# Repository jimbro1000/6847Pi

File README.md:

# Motorola 6847P Replacement #

## Background ##

The 6847P is fairly ubiquitous in the history of 70s/80s home computers and while it provides a simple solution to
video signal generation although with fairly basic capabilities in comparison with the custom video solutions
of other 80s home computers.

In terms of availability, the chip is easily obtained and due to reliability, rarely needs replacing. Compared
with the Sinclair ULA or Commodore VIC chips this is a bulletproof system *but* reliability does not equate to
desirability.

The PAL version of the output generated has a very limited palette when in higher resolution modes, the NTSC
version of the output utilises video artifacts to provide a wider capability but is still well behind its
competitors.

## Building a better 6847 ##

There are a number of things that can be done to improve on the design and the availability of high performance,
cheap microcontrollers means it is fairly simple to build a custom VDG that exhibits the same external behaviour
while operating in a completely custom manner internally.

Custom fonts are a basic starting point, custom palettes are equally simple but there is scope in the system to
incorporate custom modes of operation provided the same addressing and timing is retained.

The essential requirement is to replace the 6847P in the Dragon range of home computers - this significantly
narrows the functional requirements of the substitute. In this scenario all addressing is performed by the
accompanying SAM (MC6883) address multiplexing chip. The system also binds pins to further simplify
implementation - INV and DD6 are combined, as are ~A/S and DD7, and ~INT/EXT with GM0. Without this there are
simply not enough GPIO pins available on the pre-built RP Pico board (as opposed to the RP2040 chip itself).

## Objectives ##

1. MVP is to reproduce the existing 6847 as per the original Motorola datasheet using the RP2040 microcontroller
2. Add custom font definition
3. Modify palette definitions per mode
4. Create custom video modes following original timing
5. Create custom video modes with novel screen construction and timing

## Signal Output ##

The 6847 provides 13 lanes of address bus to reference memory - this maps to the first 8k of the regular 16bit
address space. If used in conjunction with the MC6883 SAM chip only the first bit is used to provided a clock
signal to an internal address counter. This allows the use of paged video memory - all on 512 byte boundaries,
potentially anywhere in the full 64k address space.

In addition, the chip provides a horizontal sync signal (consumed by the SAM)

Fully implemented the data output requires 14 gpio pins. Simplifying the implementation in conjunction with a
SAM reduces the pin count to just 2.

## Signal Input ##

The 6847 requires a clock input (CLK), 8 bits of data bus (DD0-DD7) and 8 bits of mode control:

* ~A/G = Alpha or Graphics
* ~A/S = Alpha or Semigraphics
* ~INT/EXT = Internal or External alphanumerics
* GM0 = Graphic Mode LSB
* GM1 = Graphic Mode Bit 1
* GM2 = Graphic Mode Bit 2 (MSB)
* CSS
* INV = Inverted Alphanumerics

~A/G, ~A/S, CSS and INV can be controlled on a character by character basis.

CSS selects between two possible alphanumeric colours - the effect
will vary depending on the graphic mode selected

| ~A/G | ~A/S | ~INT/EXT | INV | GM2 | GM1 | GM0 | Mode                           | Colours | Page Size |
|:----:|:----:|:--------:|:---:|:---:|:---:|:---:|:-------------------------------|:-------:|:---------:|
|  0   |  0   |    0     |  0  |  X  |  X  |  X  | Internal Alphanumeric          |    2    |    512    |
|  0   |  0   |    0     |  1  |  X  |  X  |  X  | Internal Alphanumeric Inverted |    2    |    512    |
|  0   |  0   |    1     |  0  |  X  |  X  |  X  | External Alphanumeric          |    2    |    512    |
|  0   |  0   |    1     |  1  |  X  |  X  |  X  | External Alphanumeric Inverted |    2    |    512    |
|  0   |  1   |    0     |  X  |  X  |  X  |  X  | Semigraphics 4                 |    8    |   1024    |
|  0   |  1   |    1     |  X  |  X  |  X  |  X  | Semigraphics 6                 |    8    |   2048    |
|  1   |  X   |    X     |  X  |  0  |  0  |  0  | 64x64 Graphics                 |    4    |   1024    |
|  1   |  X   |    X     |  X  |  0  |  0  |  1  | 128x64 Graphics                |    2    |   1024    |
|  1   |  X   |    X     |  X  |  0  |  1  |  0  | 128x64 Graphics                |    4    |   2048    |
|  1   |  X   |    X     |  X  |  0  |  1  |  1  | 128x96 Graphics                |    2    |   1536    |
|  1   |  X   |    X     |  X  |  1  |  0  |  0  | 128x96 Graphics                |    4    |   3072    |
|  1   |  X   |    X     |  X  |  1  |  0  |  1  | 128x192 Graphics               |    2    |   3072    |
|  1   |  X   |    X     |  X  |  1  |  1  |  0  | 128x192 Graphics               |    4    |   6144    |
|  1   |  X   |    X     |  X  |  1  |  1  |  1  | 256x192 Graphics               |    2    |   6144    |

The control input consumes 15 GPIO pins.

## Video Output ##

The 6847 has three output lines - Luminance (Y), ∅ A and ∅ B.

The three signals combine to provide 9 colours - black, green, yellow, blue, red, buff (white), cyan, magenta
and orange.

Y is a 6 level analogue signal, A is a 3 level analogue signal, B is a 4 level analogue signal. Not all signal
combinations are valid for the primary display area. For the main display only 4 levels are needed, the other
two levels are used for signal blanking and sync.

| Colour  | Y |  A  | B |  
|:--------|:-:|:---:|:-:|  
| Black   | 5 | 0/1 | 2 |  
| Green   | 1 |  0  | 0 |  
| Yellow  | 0 |  1  | 0 |  
| Blue    | 2 |  1  | 3 |  
| Red     | 2 |  2  | 2 |  
| Buff    | 0 |  1  | 2 |  
| Cyan    | 1 |  0  | 2 |  
| Magenta | 1 |  2  | 3 |  
| Orange  | 1 |  2  | 0 |  

Using the original datasheet for reference the default output is for NTSC and requires a timing phase
difference between the Y, A and B signals. Y leads the trio, B follows, then A. The Y-B delay is half
the rise/fall time of Y, while the B-A delay is fully the sum of Y-B and the rise/fall time of B.

To achieve an analogue signal output from the microcontroller the signal must be synthesized from a
group of digital GPIO pins.

For the 6 level Y output 3 pins are needed (actually achieves 8 levels). For A and B where 3 or 4 levels are
required then just 2 gpio pins each is needed. This consumes a total of 7 GPIO pins.

## Total GPIO Pin Requirements ##

Data input needs 14 or 2 GPIO pins - for the purposes of the MVP this will use the simple 2 pin
version. Control input requires 15 GPIO pins. Video output requires 7 pins. The grand total of 24 pins.

The initial choice of the RP2040 provides 30 GPIO pins - this is adequate for the simple implementation but is
inadequate for the full pin requirement of 36 pins.

### 6847 to GPIO pin mapping ###

|  6847 pin   |   RP2040 pin    |   RP Pico Pin    |
|:-----------:|:---------------:|:----------------:|
|    VSS 1    |     VSS 57      |      Gnd 38      |
|    DD6 2    |     GPIO6 8     |      GP6 9       |
|    DD0 3    |     GPIO0 2     |      GP0 1       |
|    DD1 4    |     GPIO1 3     |      GP1 2       |
|    DD2 5    |     GPIO2 4     |      GP2 4       |
|    DD3 6    |     GPIO3 5     |      GP3 5       |
|    DD4 7    |     GPIO4 6     |      GP4 6       |
|    DD5 8    |     GPIO5 7     |      GP5 7       |
|    CHB 9    |     GPIO11      |     GP11 15      |
|    B 10     | GPIO18-19 29-30 |  GP18-19 24-25   |
|    A 11     | GPIO20-21 31-32 |  GP20-21 26-27   |
|   ~MS 12    |    GPIO13 16    |     GP13 17      |
|   DA5 13    |        -        |        -         |
|   DA6 14    |        -        |        -         |
|   DA7 15    |        -        |        -         |
|   DA8 16    |        -        |        -         |
|   VCC 17    |        ?        |     Vbus 40      |
|   DA9 18    |        -        |        -         |
|   DA10 19   |        -        |        -         |
|   DA11 20   |        -        |        -         |
|   DA12 21   |        -        |        -         |
|   DA0 22    |    GPIO17 28    |     GP17 22      |
|   DA1 23    |        -        |        -         |
|   DA2 24    |        -        |        -         |
|   DA3 25    |        -        |        -         |
|   DA4 26    |        -        |        -         |
|   GM2 27    |    GPIO10 13    |     GP10 14      |
|    Y 28     | GPIO26-28 38-40 | GP26-28 31,32,34 |
|   GM1 29    |    GPIO9 12     |      GP9 12      |
|   GM0 30    |    GPIO8 11     |      GP8 11      |
| ~INT/EXT 31 |    GPIO8 11     |      GP8 11      |
|   INV 32    |     GPIO6 8     |      GP6 9       |
|   CLK 33    |    GPIO15 18    |     GP15 20      |
|   ~A/S 34   |     GPIO7 9     |      GP7 10      |
|   ~A/G 35   |    GPIO14 17    |     GP14 19      |
|   ~RP 36    |        -        |        -         |
|   ~FS 37    |    GPIO13 16    |     GP13 17      |
|   ~HS 38    |    GPIO16 27    |     GP16 21      |
|   CSS 39    |    GPIO17 28    |     GP17 22      |
|   DD7 40    |     GPIO7 9     |      GP7 10      |

Unused GPIO pins: 12 22 (23 24)

## 6847 video output levels ##

| Color       |  Y    | phi A | phi B |
|:------------|:-----:|:-----:|:-----:|
| Green       | 0.54  | 1.0   | 1.0   |
| Yellow      | 0.42  | 1.0   | 1.5   |
| Blue        | 0.72  | 2.0   | 1.5   |
| Red         | 0.72  | 1.5   | 2.0   |
| Buff        | 0.42  | 1.5   | 1.5   |
| Cyan        | 0.54  | 1.5   | 1.5   |
| Magenta     | 0.54  | 2.0   | 2.0   |
| Orange      | 0.54  | 1.0   | 2.0   |
| Black       | 0.72  | 1.5   | 1.5   |
| Dark Green  | 0.72  | 1.0   | 1.0   |
| Dark Orange | 0.72  | 1.0   | 2.0   |

Values for Y, phi A and phi B are in volts

### Y DAC ###

The 3 GPIO outputs can be converted to an analogue output using a resistor ladder array

GPIO 26 - 2kohm

GPIO 27 - 1kohm

GPIO 28 - 499ohm

Result is 8 levels from 0 to 7 - only the values 0 to 5 are needed. The output at level
5 needs to be peak output, to achieve this some level mapping is needed.

| level | pin 2 | pin 1 | pin 0 | target | output |
|:-----:|:-----:|:-----:|:-----:|:------:|:------:|
| 0     | 0     | 0     | 0     | 0%     | 0%     |
| 1     | 0     | 0     | 1     | 20%    | 14.2%  |
| 2     | 0     | 1     | 1     | 40%    | 42.8%  |
| 3     | 1     | 0     | 0     | 60%    | 57.1%  |
| 4     | 1     | 1     | 0     | 80%    | 85.7%  |
| 5     | 1     | 1     | 1     | 100%   | 100%   |

### A and B DAC ###

The outputs both use the same arrangement with just 2 pins each

GPIO 18, 20 - 1kohm

GPIO 19, 21 - 499ohm

Result on each pair is 4 levels from 0 to 3

The output for B can be direct but A only needs 3 levels which needs
mapping again.

| level | pin 21 | pin 20 | target | output |
|:-----:|:------:|:------:|:------:|:------:|
| 0     | 0      | 0      | 0%     | 0%     |
| 1     | 1      | 0      | 50%    | 66.6%  |
| 2     | 1      | 1      | 100%   | 100%   |

## Phase 2 ##

The next objective of development is to replace the LM889 composite modulator with the more modern AD724JR,
the important detail here is that the AD724JR requires an RGB input instead of the YAB signals normally
produced by the original 6847P. This in turn means we have a proper RGB signal to consume externally, not
just by the AD724JR which gives us two bonuses for the price of one.

RGB output from the RP2040 is an established capability so in many ways this is actually simplifying the
necessary work.

The complicating point here is that an 8 colour output is nice and simple and needs just 2 bits per
component channel but the Dragon needs 9 colours (actually it is more than this as we have three shades of
black generated in normal output and two different shades of orange - even if the normal green and bright
orange are not generated on the same screen mode). Nonetheless, if the original output is to be retained
there must be scope in the output signal to do this.

Approximation of output levels per channel for each colour:

| Colour        | Red  | Green | Blue  |
|:-------------:|:----:|:-----:|:-----:|
| Black         | 0%   | 0%    | 0%    |
| Red           | 75%  | 0%    | 12%   |
| Green         | 0%   | 100%  | 0%    |
| Blue          | 12%  | 0%    | 75%   |
| Yellow        | 100% | 100%  | 25%   |
| Buff          | 100% | 100%  | 100%  |
| Orange        | 100% | 25%   | 0%    |
| Cyan          | 0%   | 87%   | 50%   |
| Magenta       | 100% | 0%    | 100%  |
| Green/Black   | 0%   | 25%   | 0%    |
| Orange/Black  | 37%  | 0%    | 0%    |
| Bright Orange | 100% | 75%   | 25%   |

The tricky part comes from the orange and off-black colours. All the others can be treated as simple, single bit output.
All three channels require 3 bits for output, two more than the YAB output in phase 1. Fortunately we have two unused
GPIO pins, and better still the desired output levels match up with the bit step values (close enough to look genuine).

Again the signal pins are building a signal through a resistor ladder:

Pin 0 -> 2k ohm  
Pin 1 -> 1k ohm  
Pin 2 -> 499 ohm  

The ladder (assuming a 75 ohm terminator) allows for a peak voltage of 0.69V

The outputs are just combined in the same way as before to create a linear DAC.

The input to the AD724JR need to be grounded via a 75ohm pull-down resistor on each signal line, and through a 0.1uF
capacitor. The concern is that the raw RGB signal is then attenuated for a parallel VGA output and may require amplifying
(to be tested). Without the AD724JR the output from the ladder DAC is sufficient to drive a VGA port directly.

The VGA output still needs a hsync and vsync signal as well, these too can be driven directly (with a 47ohm resistor each),
the input to the AD724JR shouldn't need the resistors in line.

## AD724JR Input ##

Beyond the RGB, Hsync and Vsync, the AD724JR video encoder doesn't need much extra. Two 5V inputs, two grounds, a timing
signal (4.43362MHz for PAL) and some fixed values for "Encode" (high for run, low for standby), "select" (low), and
"standard" (low for PAL).

## AD724JR Output ##

The encoder provides three signals for two independent outputs. The only one of these needed is "COMP" - a combined
composite output. The other two are isolated chrominance and luminance outputs used in s-video.

Using the composite output on the AD724JR means the carefully controlled, phase matched Y/A/B output can be removed from
the Pico's responsibility. The composite output can be fed directly to the monitor port instead, although this then would
require removing or disabling the onboard signal encoder (LM1889). The new output line can be supplied directly to the
video half of the power board (pin 6). If the modulator is to be retained it would need to be fed to the base pin of TR4,
this then allows the AD724JR to drive composite and rf output. The simplest point to inject the signal would be
pin 10 (todo: verify pin 10 or 11) of the vacated LM1889 position but this then feeds through a maze of crude amplifying
transistors (TR2 and TR3) likely to destroy the quality of the signal given this task has already been performed by the
AD724JR. Given the likelihood of needing a modulated RF output it is pretty much a moot point unless a need for nostalgic
completeness is present.

Note: the output levels are double the normal strength to accommodate 75ohm remote termination

## Adopting PICOVGA library ##

Rather than write a custom set of PIO routines and supporting C code, the quickest route to production is to adopt some
ready made code in the form of PICOVGA. This is a swiss army knife approach to rendering to VGA but solves all of the
timing problems.

The primary concession at this point is that the video must render at 60Hz which makes PAL video output ugly. The next
point is that the pixel colour is strictly 8-bit instead of 9-but (RRRGGGBB instead of RRRGGGBBB). This is not a terrible
problem given the 8-bit colour approach is widely used and as demonstrated by the many demonstration projects, 256 colours
is plenty for the immediate needs of just 12 in the 6847 palette. Even including 4 extra for the NTSC artifact colours
there is plenty of scope to play with.

[PICOVGA Library](https://www.breatharian.eu/hw/picovga/index_en.html)

One of the big advantages here is that this generates the same data as required for the AD724 modulator so composite
and S-Video output is still possible (with or without audio).

## Ditching VGA for DVI ##

The alternative to VGA is to use a DVI library to perform the same task - and since it already exists this is not a huge
task. The IO requirements for DVI remain much the same 8 bits of data (4 differential pairs) and the HPD signal.

The downside to using DVI is a lack of support for an audio channel and similarly no support for other formats. It is
possible to blend an audio channel into an HDMI format (based on the DVI signal) but this requires additional hardware.

[PICODVI Library](https://github.com/Wren6991/PicoDVI)

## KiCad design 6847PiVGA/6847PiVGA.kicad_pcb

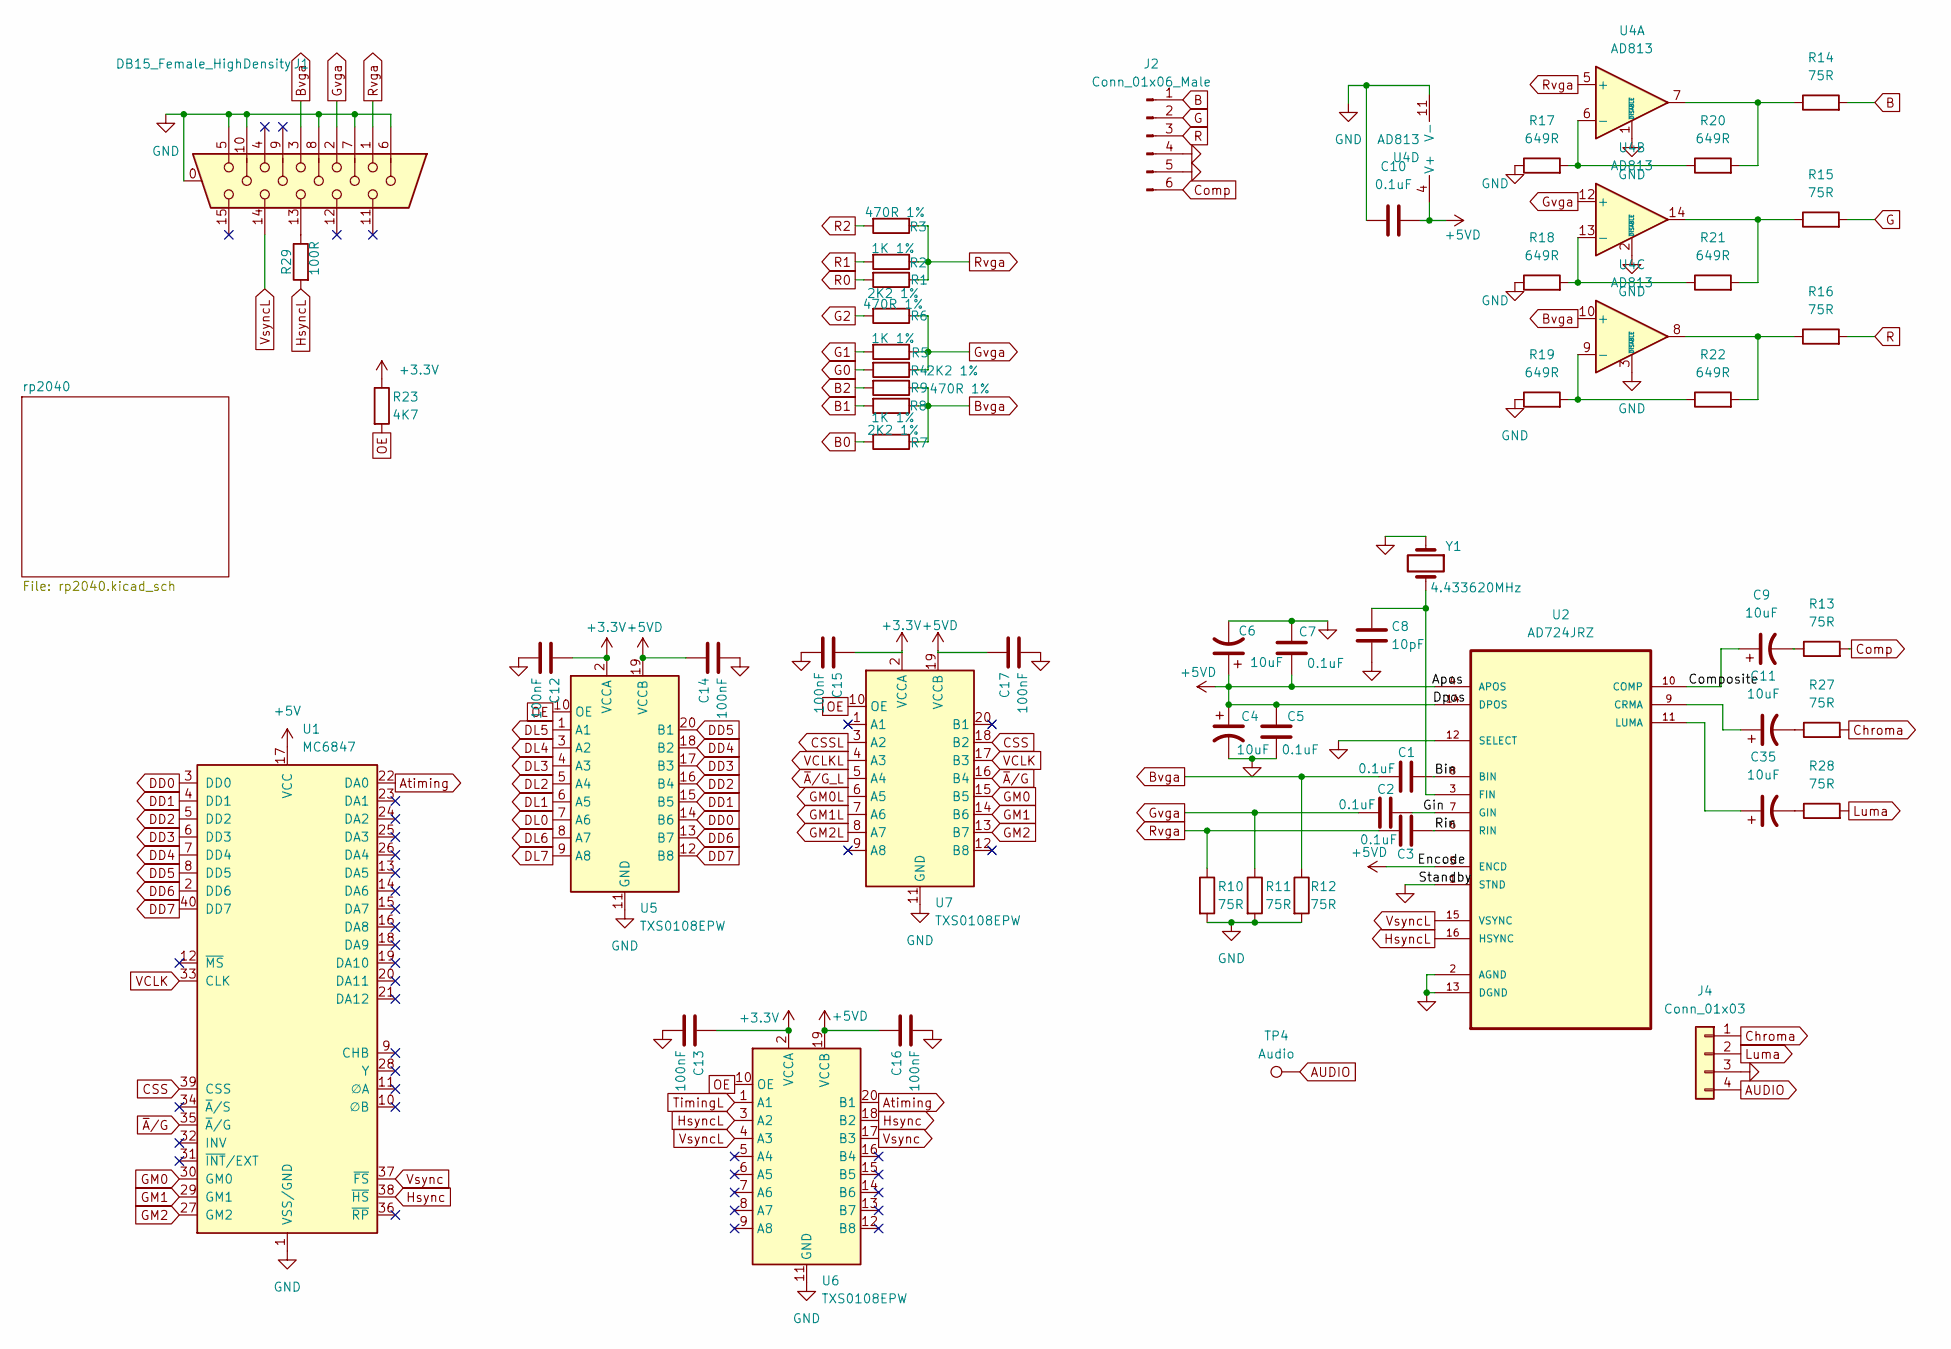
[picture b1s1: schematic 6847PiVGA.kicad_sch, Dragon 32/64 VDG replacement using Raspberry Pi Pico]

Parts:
C1, C2, C3, C5, C7, C10: 0.1uF; C_0805_2012Metric
C4, C6, C9, C11, C35: 10uF; CP_EIA-3216-10_Kemet-I_Pad1.58x1.35mm_HandSolder
C8: 10pF; C_0805_2012Metric
C12, C13, C14, C15, C16, C17: 100nF; C_0805_2012Metric
J1: DB15_Female_HighDensity; DSUB-15-HD_Female_Horizontal_P2.29x1.98mm_EdgePinOffset3.03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
J2: Conn_01x06_Male; PinHeader_1x06_P2.54mm_Vertical
J4: Conn_01x03; PinHeader_1x04_P2.54mm_Vertical
R1, R4, R7: 2K2 1%; R_0805_2012Metric
R2, R5, R8: 1K 1%; R_0805_2012Metric
R3, R6, R9: 470R 1%; R_0805_2012Metric
R10, R11, R12, R13, R14, R15, R16, R27, R28: 75R; R_0805_2012Metric
R17, R18, R19, R20, R21, R22: 649R; R_0805_2012Metric
R23: 4K7; R_0805_2012Metric
R29: 100R; R_0805_2012Metric
TP4: Audio; TestPoint_Loop_D1.80mm_Drill1.0mm_Beaded
U1: MC6847; DIP-40_W15.24mm
U2: AD724JRZ; SOIC-16W_7.5x10.3mm_P1.27mm; MPN AD724JRZ
U4: AD813; SOIC-14_3.9x8.7mm_P1.27mm
U5, U6, U7: TXS0108EPW; TSSOP-20_4.4x6.5mm_P0.65mm
Y1: 4.433620MHz; Crystal_SMD_0603-2Pin_6.0x3.5mm

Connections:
+3.3V: C12.1, C13.1, C15.1, R23.1, U5.2 (VCCA), U6.2 (VCCA), U7.2 (VCCA)
+5V: U1.17 (VCC); also elsewhere on the board
+5VD: C4.1, C5.2, C6.1, C7.2, C10.1, C14.1, C16.1, C17.1, U2.4 (APOS), U2.5 (ENCD), U2.14 (DPOS), U4.4 (V+), U5.19 (VCCB), U6.19 (VCCB), U7.19 (VCCB); also elsewhere on the board
/Bin: C1.1, U2.8 (BIN)
/Composite: C9.1, U2.10 (COMP)
/Gin: C2.1, U2.7 (GIN)
/Rin: C3.1, U2.6 (RIN)
AUDIO: J4.4, TP4.1
Atiming: U1.22 (DA0), U6.20 (B1)
B: J2.1, R14.2
B0: R7.2; also elsewhere on the board
B1: R8.2; also elsewhere on the board
B2: R9.2; also elsewhere on the board
Bvga: C1.2, J1.3, R7.1, R8.1, R9.1, R12.1, U4.10 (+)
CSS: U1.39 (CSS), U7.18 (B2)
CSSL: U7.3 (A2); also elsewhere on the board
Chroma: J4.1, R27.2
Comp: J2.6, R13.2
DD0: U1.3 (DD0), U5.14 (B6)
DD1: U1.4 (DD1), U5.15 (B5)
DD2: U1.5 (DD2), U5.16 (B4)
DD3: U1.6 (DD3), U5.17 (B3)
DD4: U1.7 (DD4), U5.18 (B2)
DD5: U1.8 (DD5), U5.20 (B1)
DD6: U1.2 (DD6), U5.13 (B7)
DD7: U1.40 (DD7), U5.12 (B8)
DL0: U5.7 (A6); also elsewhere on the board
DL1: U5.6 (A5); also elsewhere on the board
DL2: U5.5 (A4); also elsewhere on the board
DL3: U5.4 (A3); also elsewhere on the board
DL4: U5.3 (A2); also elsewhere on the board
DL5: U5.1 (A1); also elsewhere on the board
DL6: U5.8 (A7); also elsewhere on the board
DL7: U5.9 (A8); also elsewhere on the board
G: J2.2, R15.2
G0: R4.2; also elsewhere on the board
G1: R5.2; also elsewhere on the board
G2: R6.2; also elsewhere on the board
GM0: U1.30 (GM0), U7.15 (B5)
GM0L: U7.6 (A5); also elsewhere on the board
GM1: U1.29 (GM1), U7.14 (B6)
GM1L: U7.7 (A6); also elsewhere on the board
GM2: U1.27 (GM2), U7.13 (B7)
GM2L: U7.8 (A7); also elsewhere on the board
GND: C4.2, C5.1, C6.2, C7.1, C8.2, C10.2, C12.2, C13.2, C14.2, C15.2, C16.2, C17.2, J1.0 (Shield), J1.5, J1.6, J1.7, J1.8, J1.10, J2.4, J2.5, J4.3, R10.2, R11.2, R12.2, R17.1, R18.1, R19.1, U1.1 (VSS/GND), U2.1 (STND), U2.2 (AGND), U2.12 (SELECT), U2.13 (DGND), U4.1 (~DISABLE), U4.2 (~DISABLE), U4.3 (~DISABLE), U4.11 (V-), U5.11 (GND), U6.11 (GND), U7.11 (GND), Y1.1; also elsewhere on the board
Gvga: C2.2, J1.2, R4.1, R5.1, R6.1, R11.1, U4.12 (+)
Hsync: U1.38 (~HS), U6.18 (B2)
HsyncL: R29.2, U2.16 (HSYNC), U6.3 (A2); also elsewhere on the board
Luma: J4.2, R28.2
unnamed: C9.2, R13.1
unnamed: C11.2, R27.1
unnamed: C35.2, R28.1
unnamed: J1.13, R29.1
unnamed: R14.1, R20.2, U4.7
unnamed: R15.1, R21.2, U4.14
unnamed: R16.1, R22.2, U4.8
unnamed: C11.1, U2.9 (CRMA)
unnamed: C8.1, U2.3 (FIN), Y1.2
unnamed: C35.1, U2.11 (LUMA)
unnamed: R17.2, R20.1, U4.6 (-)
unnamed: R18.2, R21.1, U4.13 (-)
unnamed: R19.2, R22.1, U4.9 (-)
OE: R23.2, U5.10 (OE), U6.10 (OE), U7.10 (OE)
R: J2.3, R16.2
R0: R1.2; also elsewhere on the board
R1: R2.2; also elsewhere on the board
R2: R3.2; also elsewhere on the board
Rvga: C3.2, J1.1, R1.1, R2.1, R3.1, R10.1, U4.5 (+)
TimingL: U6.1 (A1); also elsewhere on the board
VCLK: U1.33 (CLK), U7.17 (B3)
VCLKL: U7.4 (A3); also elsewhere on the board
Vsync: U1.37 (~FS), U6.17 (B3)
VsyncL: J1.14, U2.15 (VSYNC), U6.4 (A3); also elsewhere on the board
~A/G: U1.35 (~A/G), U7.16 (B4)
~A/G_L: U7.5 (A4); also elsewhere on the board

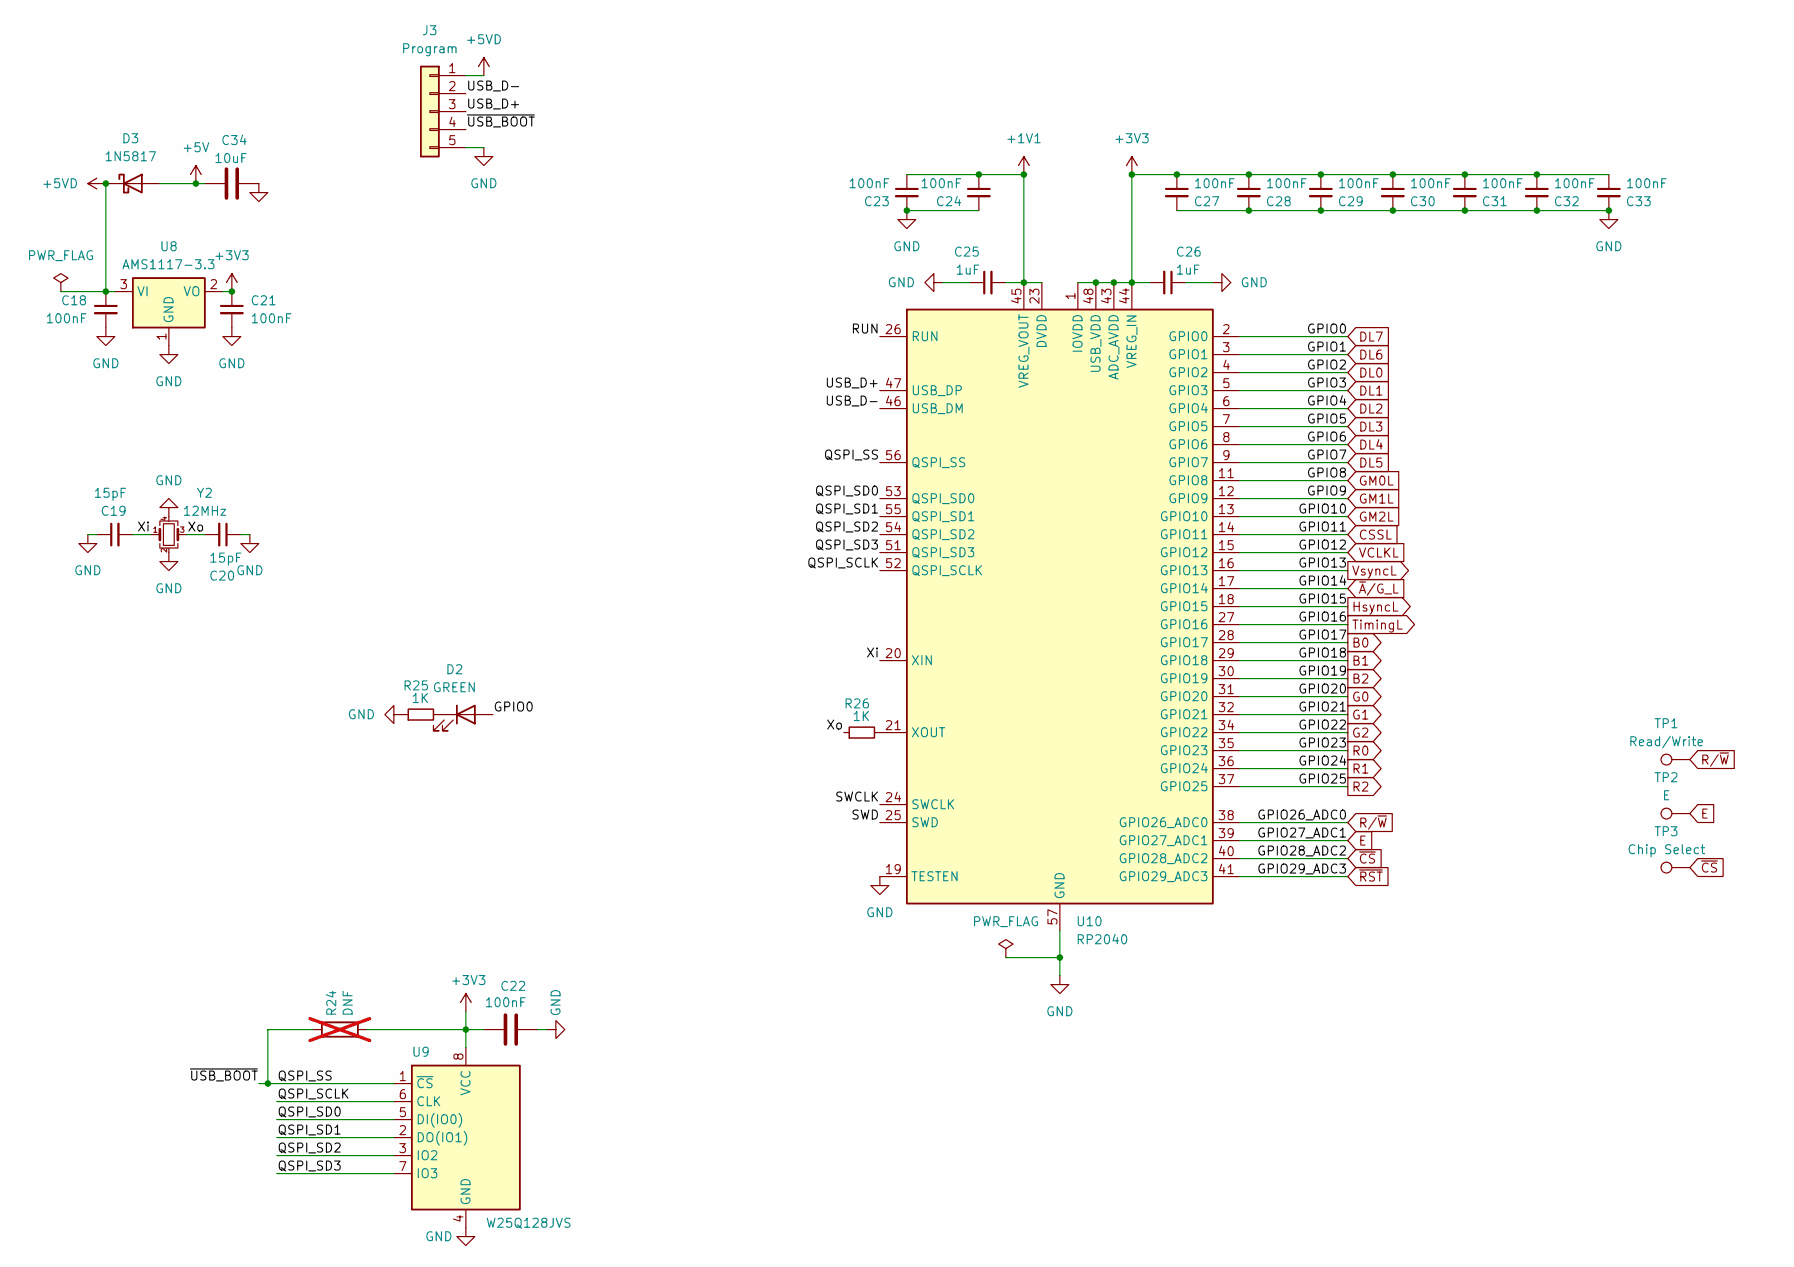
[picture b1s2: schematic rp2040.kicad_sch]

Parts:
C18, C21: 100nF; C_0805_2012Metric_Pad1.18x1.45mm_HandSolder; LCSC C113803
C19, C20: 15pF; C_0603_1608Metric_Pad1.08x0.95mm_HandSolder; LCSC C694267
C22: 100nF; C_0805_2012Metric_Pad1.18x1.45mm_HandSolder; LCSC C361202
C23, C24: 100nF; C_0603_1608Metric_Pad1.08x0.95mm_HandSolder
C25: 1uF; C_0603_1608Metric_Pad1.08x0.95mm_HandSolder
C26: 1uF; C_0603_1608Metric_Pad1.08x0.95mm_HandSolder; LCSC C2175508
C27, C28, C29, C30, C31, C32, C33: 100nF; C_0603_1608Metric_Pad1.08x0.95mm_HandSolder; LCSC C361202
C34: 10uF; C_0805_2012Metric
D2: GREEN; D_0805_2012Metric_Pad1.15x1.40mm_HandSolder; DigiKey 732-4980-1-ND
D3: 1N5817; D_0805_2012Metric_Pad1.15x1.40mm_HandSolder
J3: Program; PinSocket_1x05_P1.27mm_Vertical
R24: DNF; R_0603_1608Metric; not fitted
R25: 1K; R_0805_2012Metric_Pad1.20x1.40mm_HandSolder; LCSC C319811
R26: 1K; R_0603_1608Metric; LCSC C319811
TP1: Read/Write; TestPoint_Loop_D1.80mm_Drill1.0mm_Beaded
TP2: E; TestPoint_Loop_D1.80mm_Drill1.0mm_Beaded
TP3: Chip Select; TestPoint_Loop_D1.80mm_Drill1.0mm_Beaded
U8: AMS1117-3.3; SOT-89-3; DigiKey 5272-AMS1117-3.3SCT-ND
U9: W25Q128JVS; SOIC-8_5.23x5.23mm_P1.27mm; LCSC C97521
U10: RP2040; QFN-56-1EP_7x7mm_P0.4mm_EP3.2x3.2mm; LCSC C2040
Y2: 12MHz; Oscillator_SMD_Abracon_ASE-4Pin_3.2x2.5mm_HandSoldering; DigiKey 535-ABM8-272-T3CT-ND

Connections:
+1V1: C23.1, C24.1, C25.2, U10.23 (DVDD), U10.45 (VREG_VOUT), U10.50 (DVDD)
+3V3: C21.1, C22.1, C26.2, C27.1, C28.1, C29.1, C30.1, C31.1, C32.1, C33.1, R24.2, U8.2 (VO), U9.8 (VCC), U10.1 (IOVDD), U10.10 (IOVDD), U10.22 (IOVDD), U10.33 (IOVDD), U10.42 (IOVDD), U10.43 (ADC_AVDD), U10.44 (VREG_IN), U10.48 (USB_VDD), U10.49 (IOVDD)
+5V: C34.1, D3.2 (A); also elsewhere on the board
+5VD: C18.1, D3.1 (K), J3.1, U8.3 (VI); also elsewhere on the board
/rp2040/QSPI_SCLK: U9.6 (CLK), U10.52 (QSPI_SCLK)
/rp2040/QSPI_SD0: U9.5 (DI(IO0)), U10.53 (QSPI_SD0)
/rp2040/QSPI_SD1: U9.2 (DO(IO1)), U10.55 (QSPI_SD1)
/rp2040/QSPI_SD2: U9.3 (IO2), U10.54 (QSPI_SD2)
/rp2040/QSPI_SD3: U9.7 (IO3), U10.51 (QSPI_SD3)
/rp2040/QSPI_SS: J3.4, R24.1, U9.1 (~CS), U10.56 (QSPI_SS)
/rp2040/RUN: U10.26 (RUN)
/rp2040/SWCLK: U10.24 (SWCLK)
/rp2040/SWD: U10.25 (SWD)
/rp2040/USB_D+: J3.3, U10.47 (USB_DP)
/rp2040/USB_D-: J3.2, U10.46 (USB_DM)
/rp2040/Xi: C19.2, U10.20 (XIN), Y2.1
/rp2040/Xo: C20.2, R26.1, Y2.3
B0: U10.28 (GPIO17); also elsewhere on the board
B1: U10.29 (GPIO18); also elsewhere on the board
B2: U10.30 (GPIO19); also elsewhere on the board
CSSL: U10.14 (GPIO11); also elsewhere on the board
DL0: U10.4 (GPIO2); also elsewhere on the board
DL1: U10.5 (GPIO3); also elsewhere on the board
DL2: U10.6 (GPIO4); also elsewhere on the board
DL3: U10.7 (GPIO5); also elsewhere on the board
DL4: U10.8 (GPIO6); also elsewhere on the board
DL5: U10.9 (GPIO7); also elsewhere on the board
DL6: U10.3 (GPIO1); also elsewhere on the board
DL7: D2.2 (A), U10.2 (GPIO0); also elsewhere on the board
E: TP2.1, U10.39 (GPIO27_ADC1)
G0: U10.31 (GPIO20); also elsewhere on the board
G1: U10.32 (GPIO21); also elsewhere on the board
G2: U10.34 (GPIO22); also elsewhere on the board
GM0L: U10.11 (GPIO8); also elsewhere on the board
GM1L: U10.12 (GPIO9); also elsewhere on the board
GM2L: U10.13 (GPIO10); also elsewhere on the board
GND: C18.2, C19.1, C20.1, C21.2, C22.2, C23.2, C24.2, C25.1, C26.1, C27.2, C28.2, C29.2, C30.2, C31.2, C32.2, C33.2, C34.2, J3.5, R25.1, U8.1 (GND), U9.4 (GND), U10.19 (TESTEN), U10.57 (GND), Y2.2, Y2.4; also elsewhere on the board
HsyncL: U10.18 (GPIO15); also elsewhere on the board
unnamed: D2.1 (K), R25.2
unnamed: R26.2, U10.21 (XOUT)
R0: U10.35 (GPIO23); also elsewhere on the board
R1: U10.36 (GPIO24); also elsewhere on the board
R2: U10.37 (GPIO25); also elsewhere on the board
R/~W: TP1.1, U10.38 (GPIO26_ADC0)
TimingL: U10.27 (GPIO16); also elsewhere on the board
VCLKL: U10.15 (GPIO12); also elsewhere on the board
VsyncL: U10.16 (GPIO13); also elsewhere on the board
~A/G_L: U10.17 (GPIO14); also elsewhere on the board
~CS: TP3.1, U10.40 (GPIO28_ADC2)
~RST: U10.41 (GPIO29_ADC3)

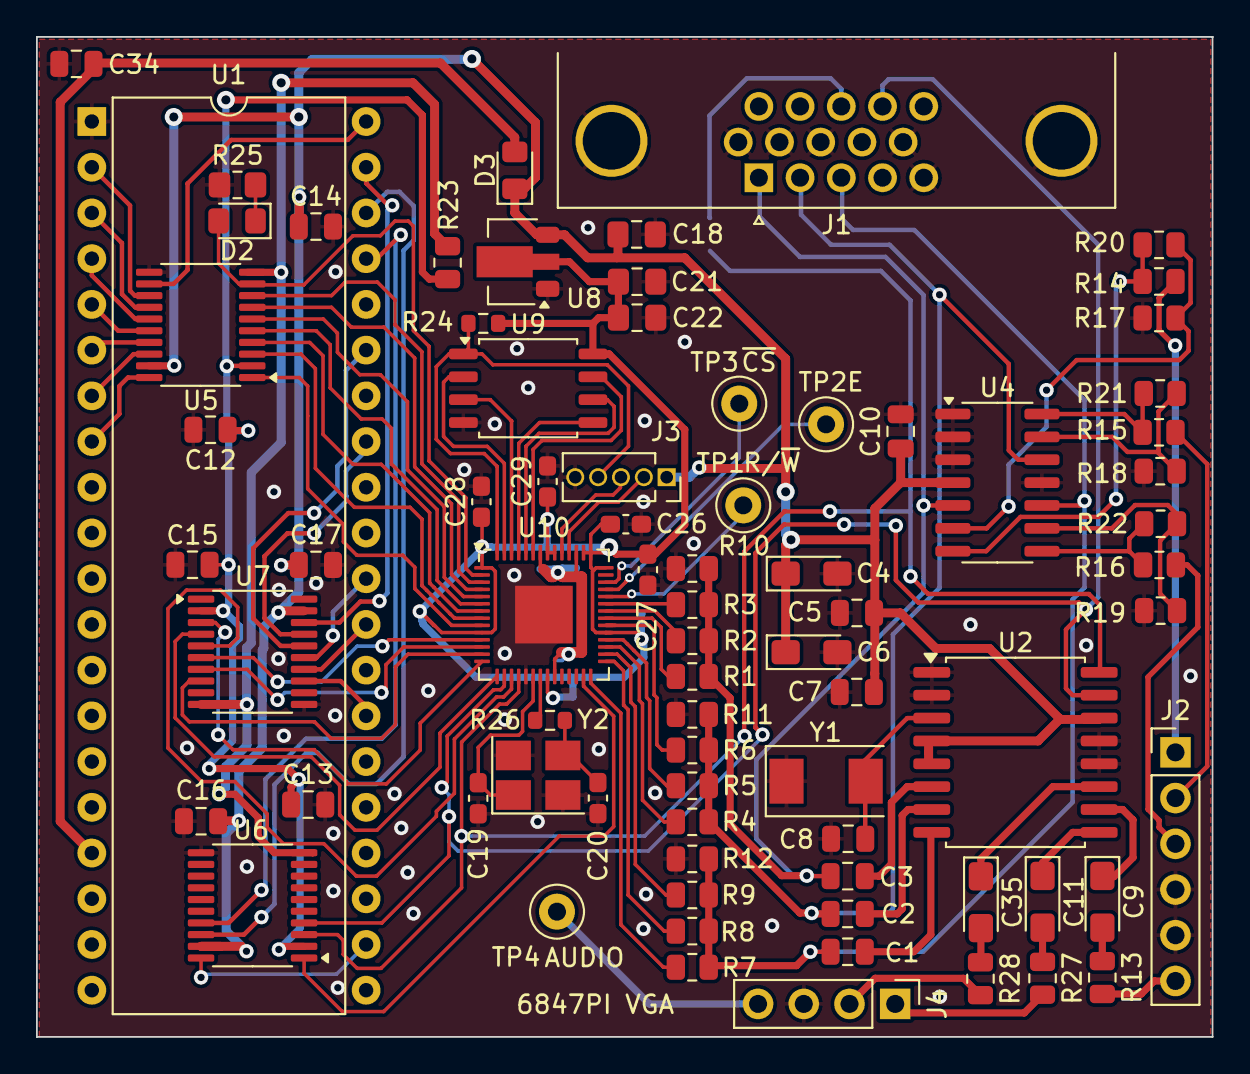
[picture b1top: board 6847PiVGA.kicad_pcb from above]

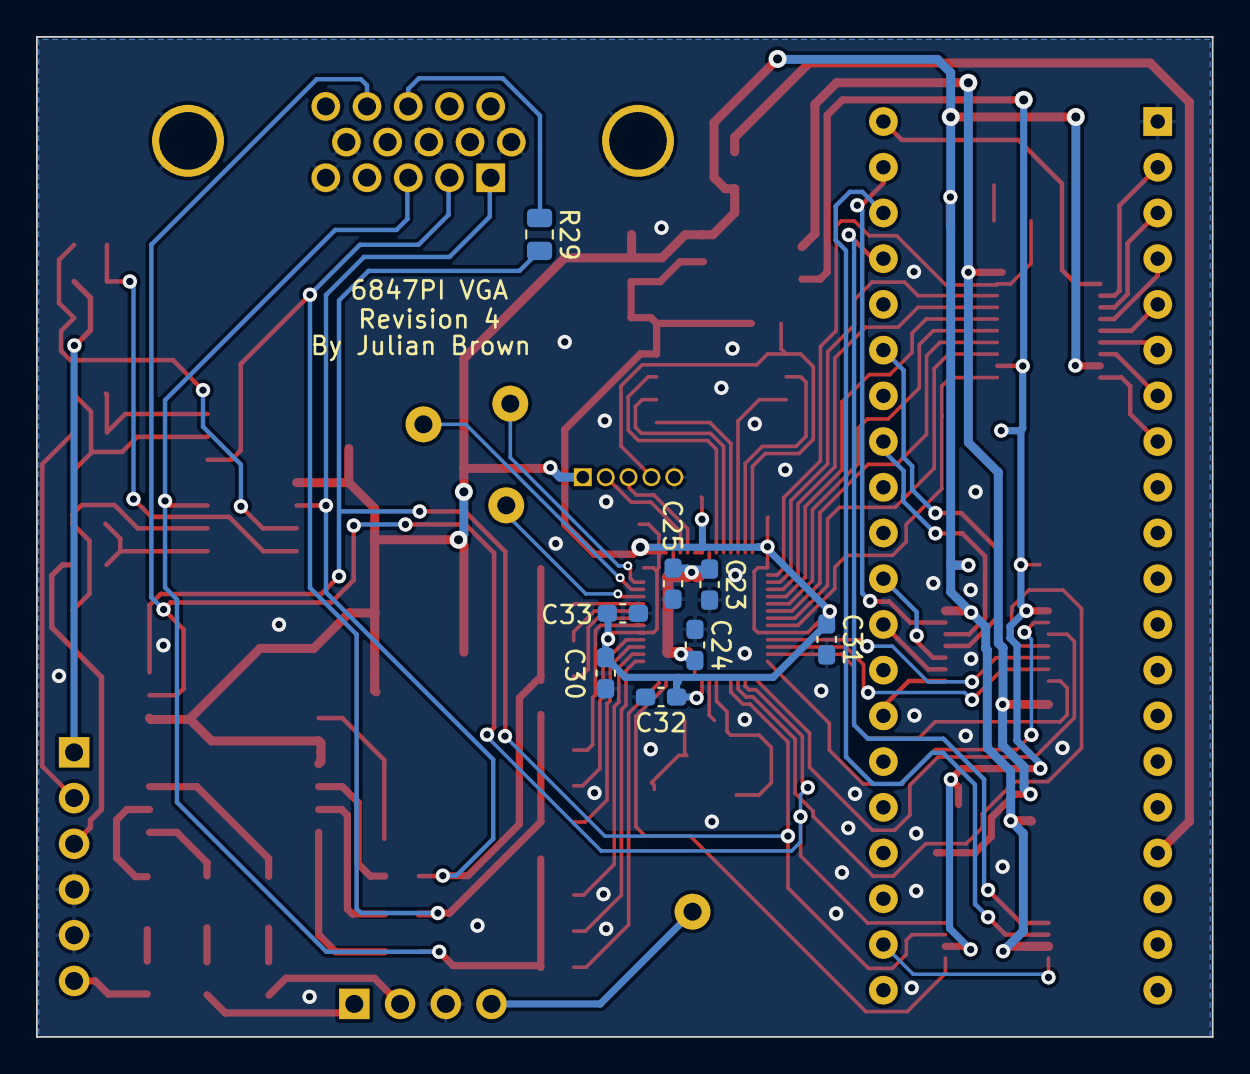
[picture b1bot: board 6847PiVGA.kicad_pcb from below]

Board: 2 copper layers, 65.3 x 55.6 mm, 85 parts (8 on the bottom side), 92 nets.

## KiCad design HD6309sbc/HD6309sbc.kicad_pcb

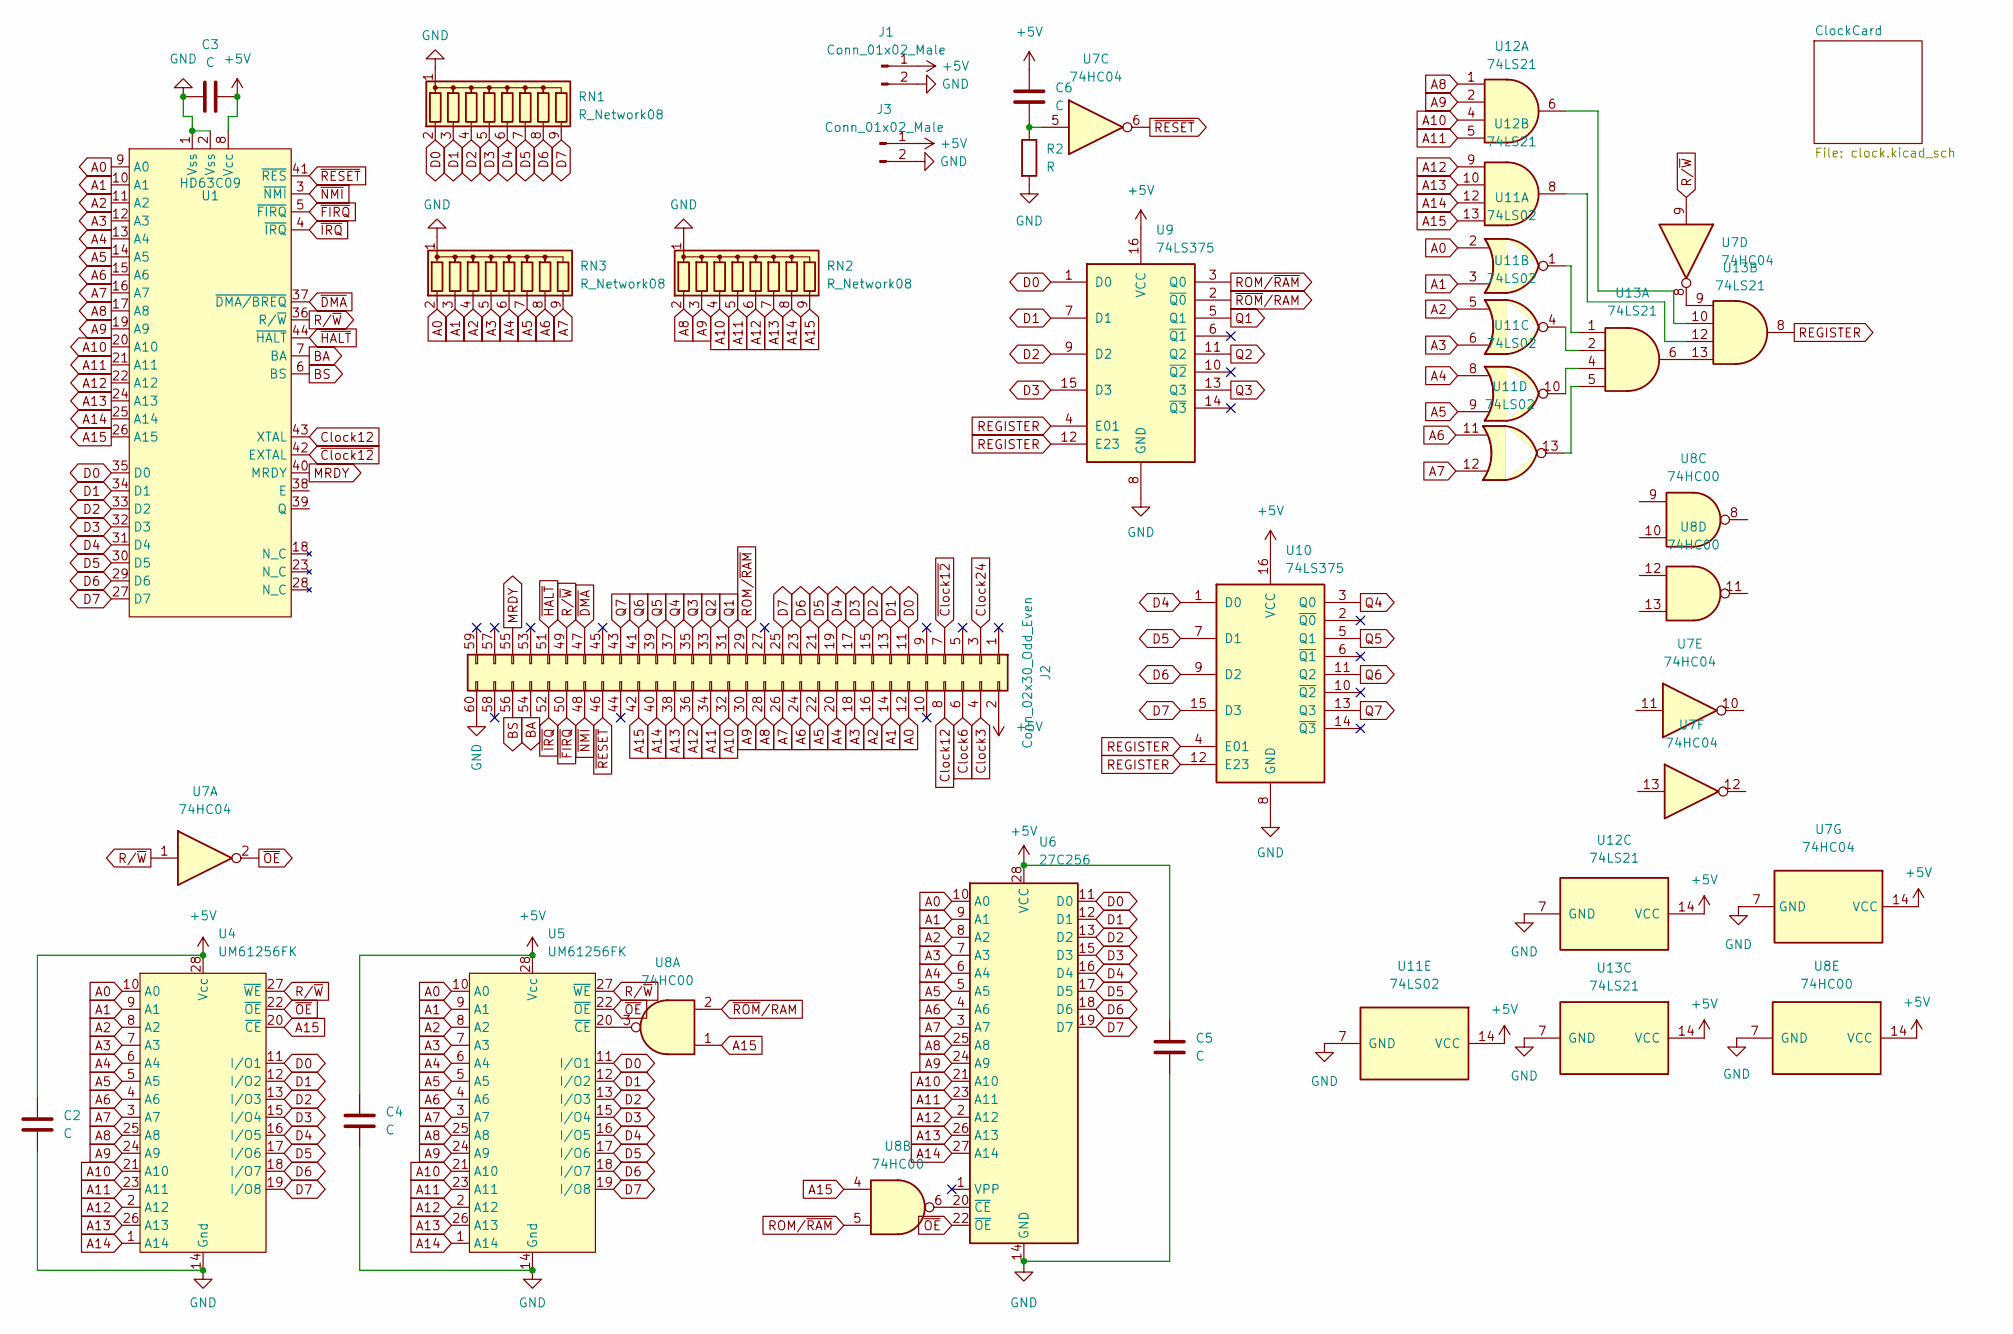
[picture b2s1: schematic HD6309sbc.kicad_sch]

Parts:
C2, C3, C4, C5, C6: C; C_0805_2012Metric
J1, J3: Conn_01x02_Male; PinHeader_1x02_P2.54mm_Vertical
J2: Conn_02x30_Odd_Even; PinHeader_2x30_P2.54mm_Vertical
R2: R; R_0805_2012Metric
RN1, RN2, RN3: R_Network08; R_Array_SIP9
U1: HD63C09; PLCC-44_THT-Socket
U4, U5: UM61256FK; DIP-28_W7.62mm
U6: 27C256; PLCC-28_THT-Socket
U7: 74HC04; SO-14_3.9x8.65mm_P1.27mm
U8: 74HC00; SO-14_3.9x8.65mm_P1.27mm
U9, U10: 74LS375; SO-16_3.9x9.9mm_P1.27mm
U11: 74LS02; SO-14_3.9x8.65mm_P1.27mm
U12, U13: 74LS21; SO-14_3.9x8.65mm_P1.27mm

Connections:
+5V: C2.1, C3.1, C4.1, C5.1, C6.1, J1.1, J2.2, J3.1, U1.8 (Vcc), U4.28 (Vcc), U5.28 (Vcc), U6.28 (VCC), U7.14 (VCC), U8.14 (VCC), U9.16 (VCC), U10.16 (VCC), U11.14 (VCC), U12.14 (VCC), U13.14 (VCC); also elsewhere on the board
A0: J2.12, RN3.2 (R1), U1.9 (A0), U4.10 (A0), U5.10 (A0), U6.10 (A0), U11.2
A1: J2.14, RN3.3 (R2), U1.10 (A1), U4.9 (A1), U5.9 (A1), U6.9 (A1), U11.3
A2: J2.16, RN3.4 (R3), U1.11 (A2), U4.8 (A2), U5.8 (A2), U6.8 (A2), U11.5
A3: J2.18, RN3.5 (R4), U1.12 (A3), U4.7 (A3), U5.7 (A3), U6.7 (A3), U11.6
A4: J2.20, RN3.6 (R5), U1.13 (A4), U4.6 (A4), U5.6 (A4), U6.6 (A4), U11.8
A5: J2.22, RN3.7 (R6), U1.14 (A5), U4.5 (A5), U5.5 (A5), U6.5 (A5), U11.9
A6: J2.24, RN3.8 (R7), U1.15 (A6), U4.4 (A6), U5.4 (A6), U6.4 (A6), U11.11
A7: J2.26, RN3.9 (R8), U1.16 (A7), U4.3 (A7), U5.3 (A7), U6.3 (A7), U11.12
A8: J2.28, RN2.2 (R1), U1.17 (A8), U4.25 (A8), U5.25 (A8), U6.25 (A8), U12.1
A9: J2.30, RN2.3 (R2), U1.19 (A9), U4.24 (A9), U5.24 (A9), U6.24 (A9), U12.2
A10: J2.32, RN2.4 (R3), U1.20 (A10), U4.21 (A10), U5.21 (A10), U6.21 (A10), U12.4
A11: J2.34, RN2.5 (R4), U1.21 (A11), U4.23 (A11), U5.23 (A11), U6.23 (A11), U12.5
A12: J2.36, RN2.6 (R5), U1.22 (A12), U4.2 (A12), U5.2 (A12), U6.2 (A12), U12.9
A13: J2.38, RN2.7 (R6), U1.24 (A13), U4.26 (A13), U5.26 (A13), U6.26 (A13), U12.10
A14: J2.40, RN2.8 (R7), U1.25 (A14), U4.1 (A14), U5.1 (A14), U6.27 (A14), U12.12
A15: J2.42, RN2.9 (R8), U1.26 (A15), U4.20 (~CE), U8.1, U8.4, U12.13
BA: J2.54, U1.7 (BA)
BS: J2.56, U1.6 (BS)
Clock3: J2.4; also elsewhere on the board
Clock6: J2.6; also elsewhere on the board
Clock12: J2.8, U1.43 (XTAL); also elsewhere on the board
Clock24: J2.3; also elsewhere on the board
D0: J2.11, RN1.2 (R1), U1.35 (D0), U4.11 (I/O1), U5.11 (I/O1), U6.11 (D0), U9.1 (D0)
D1: J2.13, RN1.3 (R2), U1.34 (D1), U4.12 (I/O2), U5.12 (I/O2), U6.12 (D1), U9.7 (D1)
D2: J2.15, RN1.4 (R3), U1.33 (D2), U4.13 (I/O3), U5.13 (I/O3), U6.13 (D2), U9.9 (D2)
D3: J2.17, RN1.5 (R4), U1.32 (D3), U4.15 (I/O4), U5.15 (I/O4), U6.15 (D3), U9.15 (D3)
D4: J2.19, RN1.6 (R5), U1.31 (D4), U4.16 (I/O5), U5.16 (I/O5), U6.16 (D4), U10.1 (D0)
D5: J2.21, RN1.7 (R6), U1.30 (D5), U4.17 (I/O6), U5.17 (I/O6), U6.17 (D5), U10.7 (D1)
D6: J2.23, RN1.8 (R7), U1.29 (D6), U4.18 (I/O7), U5.18 (I/O7), U6.18 (D6), U10.9 (D2)
D7: J2.25, RN1.9 (R8), U1.27 (D7), U4.19 (I/O8), U5.19 (I/O8), U6.19 (D7), U10.15 (D3)
GND: C2.2, C3.2, C4.2, C5.2, J1.2, J2.60, J3.2, R2.2, RN1.1 (common), RN2.1 (common), RN3.1 (common), U1.1 (Vss), U1.2 (Vss), U4.14 (Gnd), U5.14 (Gnd), U6.14 (GND), U7.7 (GND), U8.7 (GND), U9.8 (GND), U10.8 (GND), U11.7 (GND), U12.7 (GND), U13.7 (GND); also elsewhere on the board
MRDY: J2.55, U1.40 (MRDY)
unnamed: C6.2, R2.1, U7.5
unnamed: U5.20 (~CE), U8.3
unnamed: U6.20 (~CE), U8.6
unnamed: U11.1, U13.1
unnamed: U11.4, U13.2
unnamed: U11.10, U13.4
unnamed: U11.13, U13.5
unnamed: U12.6, U13.10
unnamed: U12.8, U13.12
unnamed: U7.8, U13.9
unnamed: U13.6, U13.13
Q1: J2.31, U9.5 (Q1)
Q2: J2.33, U9.11 (Q2)
Q3: J2.35, U9.13 (Q3)
Q4: J2.37, U10.3 (Q0)
Q5: J2.39, U10.5 (Q1)
Q6: J2.41, U10.11 (Q2)
Q7: J2.43, U10.13 (Q3)
REGISTER: U9.4 (E01), U9.12 (E23), U10.4 (E01), U10.12 (E23), U13.8
ROM/~RAM: J2.29, U8.5, U9.3 (Q0)
R/~W: J2.49, U1.36 (R/~W), U4.27 (~WE), U5.27 (~WE), U7.1, U7.9
~Clock12: J2.7, U1.42 (EXTAL); also elsewhere on the board
~DMA: J2.47, U1.37 (~DMA/BREQ)
~FIRQ: J2.50, U1.5 (~FIRQ)
~HALT: J2.51, U1.44 (~HALT)
~IRQ: J2.52, U1.4 (~IRQ)
~NMI: J2.48, U1.3 (~NMI)
~OE: U4.22 (~OE), U5.22 (~OE), U6.22 (~OE), U7.2
~RESET: J2.46, U1.41 (~RES), U7.6
~ROM/RAM: U8.2, U9.2 (~Q0)
